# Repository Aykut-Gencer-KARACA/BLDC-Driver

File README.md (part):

<div align="center">

<br/>

<br/><br/>

**Sıfırdan tasarlanmış bir fırçasız DC (BLDC) motor sürücüsü.**<br/>
Hall sensörü olmadan, boştaki fazın back-EMF sıfır geçişini okuyarak rotor konumunu tahmin eder.

<br/>

<sub>PCB'nin Blender'da hazırlanmış 3D render'ı · tam çözünürlüklü video için görsele tıklayın</sub>

</div>

<!--
  ────────────────────────────────────────────────────────────────────────────
  OYNATILABİLİR VİDEO (isteğe bağlı)
  GitHub, repodaki .mp4 dosyalarını README içinde oynatıcı olarak GÖSTERMEZ.
  Oynatıcı istiyorsanız:
    1) GitHub'da README.md'yi web editöründe açın (kalem simgesi).
    2) assets/pcb-render.mp4 dosyasını editöre sürükleyip bırakın.
    3) Oluşan https://github.com/user-attachments/assets/... satırını
       aşağıdaki "VIDEO_LINKI_BURAYA" satırının yerine koyun (tek başına, kendi satırında).
    4) Bu yorum bloğunu silebilirsiniz.
  ────────────────────────────────────────────────────────────────────────────
-->

<!-- VIDEO_LINKI_BURAYA -->

## İçindekiler

- [Genel bakış](#-genel-bakış)
- [Öne çıkanlar](#-öne-çıkanlar)
- [Sistem mimarisi](#-sistem-mimarisi)
- [Six-step komütasyon](#-six-step-komütasyon)
- [Donanım](#-donanım)
- [Tasarım hesapları](#-tasarım-hesapları)
- [Pin haritası](#-pin-haritası)
- [PCB](#-pcb)
- [Firmware gereksinimleri](#-firmware-gereksinimleri)
- [Malzeme listesi](#-malzeme-listesi)
- [Depo yapısı](#-depo-yapısı)

## ◆ Genel bakış

Bu proje, bir **A2212 1000 KV** fırçasız motoru **3S LiPo** batarya ile sürmek için tasarlanmış bir ESC'dir (Electronic Speed Controller). Kart; güç girişi koruması, iki ayrı regülatör, 3 fazlı MOSFET köprüsü, faz başına bağımsız akım ölçümü, back-EMF algılama ve bir **STM32F405** mikrodenetleyiciyi tek bir PCB üzerinde topluyor.

Tasarımdaki her değer bir hesaba dayanıyor: MOSFET seçiminden bootstrap kondansatörüne, dead-time'dan ferrit bead bastırma oranına kadar kararların gerekçesi [Tasarım hesapları](#-tasarım-hesapları) bölümünde; tüm türetimler adım adım [Hesaplama Notları](Tactical%20Calculation%20Reports.pdf) dosyasında.

| Özellik | Değer |
|---|---|
| **Kontrol yöntemi** | Sensörsüz six-step (trapezoidal), back-EMF sıfır geçişi |
| **Giriş gerilimi** | 3S LiPo · 11.1 V nominal · 12.6 V maksimum |
| **Faz akımı** | 10 A sürekli · 12 A tepe (tasarım hedefi) |
| **Anahtarlama** | 30 kHz, center-aligned PWM |
| **Dead-time** | 2 katman: TIM1 DTG ≈ 1 µs + DRV8300 sabit ≈ 215 ns (tipik) |
| **Akım ölçümü** | 3 × low-side şönt (10 mΩ) + 3 × INA180A1 (20 V/V), eşzamanlı örnekleme |
| **Hız ayarı** | Panel montaj 10 kΩ potansiyometre |
| **Programlama** | SWD (ST-Link V2) |

## ◆ Öne çıkanlar

<table>
<tr>
<td width="50%" valign="top">

**Katmanlı giriş koruması**<br/>
TVS diyot (SMBJ20A, 32.4 V clamp), 20 A SMD sigorta ve P-kanal ters polarite MOSFET. Hot-plug ve anahtarlama kaynaklı gerilim darbelerine karşı koruma.

</td>
<td width="50%" valign="top">

**Faz başına eşzamanlı akım ölçümü**<br/>
Üç şönt akımı üç ayrı ADC'ye dağıtıldı (ADC1/2/3) ve her birinde **Rank 1** kanalı. TIM1 CH4 tetiklediği anda üç faz aynı anda örnekleniyor, fazlar arası zaman kayması yok.

</td>
</tr>
<tr>
<td valign="top">

**Isıl hesabı yapılmış MOSFET seçimi**<br/>
DON100N04 (40 V, < 3.5 mΩ, **Q<sub>g</sub> ≈ 40 nC** @ 10 V). 10.5 A'de MOSFET başına ≈ 0.39 W (25 °C); sıcakken (4.46 mΩ) ≈ 0.49 W ve 40 °C ortamda T<sub>J</sub> ≈ 65 °C. Bu kartta tek MOSFET'in ısıl sınırı ≈ 22 A.

</td>
<td valign="top">

**Temiz analog besleme**<br/>
VDDA hattı ferrit bead + 100 nF + 1 µF ile buck ripple'ından ayrıldı. 500 kHz'de tahmini **30–60 kat bastırma** (geçen kısım ≈ %1.6–3). ADC referansı ve CSA beslemesi aynı hattan: ölçüm oransal (ratiometric).

</td>
</tr>
<tr>
<td valign="top">

**Hesaplanmış bootstrap**<br/>
C<sub>BOOT,min</sub> ≈ 47 nF (TI'ın 1 V dalgalanma kuralı), seçilen 100 nF ile **~2× pay** ve ≈ 0.47 V dalgalanma. Üst kol kesintisiz açık kalamayacağı için %100 duty kullanılmıyor.

</td>
<td valign="top">

**Sanal nötr ile back-EMF algılama**<br/>
Faz başına 20 kΩ / 4.99 kΩ bölücü 12.6 V'u ≈ 2.52 V'a indiriyor; 3 × 20 kΩ + 1.65 kΩ'luk sanal nötr aynı ölçekte (sapma ≈ %0.7). Boştaki fazın nötrü kestiği an sıfır geçişi.

</td>
</tr>
</table>

## ◆ Sistem mimarisi

Güç yolu soldan sağa akıyor: batarya, sırasıyla sigorta (F1), TVS diyodu (D1) ve ters polarite MOSFET'inden (Q7) geçip `V_BUS` barasına ulaşıyor. Bu baradan üç kol ayrılıyor:

- **TPS54202 buck** → 3.3 V (MCU, CSA'lar, potansiyometre) · 500 kHz senkron
- **BA00BC0WFP LDO** → 8 V GVDD (DRV8300 gate sürme beslemesi) · ≈ 5 mA tipik, en fazla ≈ 11 mA yük
- **3 faz köprü** → motor fazları A / B / C

STM32, TIM1'in 6 tamamlayıcı PWM çıkışıyla DRV8300'ü sürüyor; DRV8300 de bootstrap üzerinden üst kol N-kanal MOSFET'lerin gate'lerini bara geriliminin üstüne taşıyor.

## ◆ Six-step komütasyon

Her elektriksel periyot altı adıma bölünüyor. Her adımda **iki faz aktif** (biri üst koldan PWM'leniyor, diğeri alt koldan sürekli iletimde), **üçüncü faz boşta** kalıyor. Boştaki fazın back-EMF'i sanal nötr seviyesini kestiği anda (sıfır geçişi) rotorun konumu biliniyor ve bir sonraki adıma geçiş zamanlanıyor.

| Adım | 1 | 2 | 3 | 4 | 5 | 6 |
|:--|:-:|:-:|:-:|:-:|:-:|:-:|
| **Üst kol (PWM)** | A | A | B | B | C | C |
| **Alt kol (açık)** | B | C | C | A | A | B |
| **Boşta (BEMF ölçümü)** | C | B | A | C | B | A |

> [!NOTE]
> Motor dururken back-EMF olmadığı için sensörsüz kontrolde **açık döngü başlatma** (open-loop ramp) gerekiyor. Motor yeterli hıza ulaşıp BEMF okunabilir hale geldiğinde kapalı döngüye geçiliyor.

## ◆ Donanım

<details open>
<summary><b>Güç katı</b></summary>
<br/>

| Blok | Parça | Not |
|---|---|---|
| Yarım köprü MOSFET'leri | 6 × **DON100N04** (DFN-8) | 40 V · < 3.5 mΩ · Q<sub>g</sub> ≈ 40 nC · gövde diyodu yeterli, harici Schottky yok |
| Gate dirençleri | 6 × 15 Ω | TI referans tasarımı ve bağımsız hesapla doğrulandı |
| Gate pull-down | 6 × 10 kΩ | Self turn-on koruması |
| Faz kondansatörleri | Faz başına 100 µF + 1 µF + 100 nF | Bulk + decoupling |

</details>

<details>
<summary><b>Gate sürücü — DRV8300</b></summary>
<br/>

- DT pini boşta (ya da GND'de): dahili dead-time ≈ 215 ns (tipik, datasheet)
- Bootstrap: 100 nF, entegre bootstrap diyodu
- GVDD: 8 V LDO çıkışı
- nFAULT çıkışı yok → donanımsal aşırı akım kesmesi (BKIN) yok; akım, şönt + INA180 zinciriyle ölçülüyor

</details>

<details>
<summary><b>Akım ölçümü</b></summary>
<br/>

- 3 × **10 mΩ / 3 W** şönt (2512), alt kol altında (low-side)
- 3 × **INA180A1** (20 V/V) — 12 A'de 2.4 V çıkış
- Çıkışta 100 Ω + 22 nF RC filtre (f<sub>c</sub> ≈ 72 kHz)
- 12-bit ADC ile çözünürlük ≈ **4 mA / LSB**

</details>

<details>
<summary><b>Back-EMF algılama</b></summary>
<br/>

- Faz başına bölücü: 20 kΩ / 4.99 kΩ → 12.6 V faz geriliminde **≈ 2.52 V** ADC girişi
- Sanal nötr: 3 × 20 kΩ yıldız + 1.65 kΩ (R<sub>n</sub> = R<sub>alt</sub>/3) → faz bölücüleriyle aynı ölçek
- Tüm dirençler ±%1; ölçek sapması ≈ %0.7

</details>

<details>
<summary><b>Mikrodenetleyici — STM32F405RGT6</b></summary>
<br/>

- Cortex-M4F · 168 MHz · 1 MB Flash · 192 KB RAM · FPU
- 8 MHz HSE kristal, 2 × 30 pF yük kondansatörü (C<sub>L</sub> = 20 pF)
- VCAP1/2: 2 × 2.2 µF X5R
- 4 × VDD'ye ayrı 100 nF, VBAT → 3.3 V + 100 nF
- NRST: 100 nF + tact switch · BOOT0: 10 kΩ ile GND
- SWD: 4 pinlik 2.54 mm header (3.3 V, SWDIO, SWCLK, GND)

</details>

<details>
<summary><b>Göstergeler (LED)</b></summary>
<br/>

| LED | Görev | Sürüş | Akım |
|---|---|---|---|
| LED1 | Güç göstergesi | 3.3 V → R38 (200 Ω) → LED1 → GND | ≈ 6.5 mA |
| LED2 | SWD aktivite göstergesi | 3.3 V → R39 (200 Ω) → LED2 → Q8 (MMBT5551, low-side) · baz SWCLK'ten R40 (10 kΩ) ile | ≈ 6.5 mA |

- LED2, debugger bağlıyken SWCLK üzerindeki trafikle yanıp söner; MCU pini harcamaz.
- Q8'in baz akımı ≈ 0.26 mA — SWCLK hattını anlamlı ölçüde yüklemez.

</details>

## ◆ Tasarım hesapları

<details>
<summary><b>Giriş koruması: sigorta, ters polarite MOSFET'i, TVS</b></summary>
<br/>

**Sigorta (F1).** 20 A, gecikmeli (time-lag), 32 V DC. Gecikmeli olması motorun kalkış anındaki kısa süreli yüksek akımda gereksiz atmayı önler; 20 A, 10 A'lik çalışma akımının iki katıdır.

**Ters polarite MOSFET'i (Q7).** Kayıp karşılaştırması, R<sub>DS(on)</sub> = 3.1 mΩ ile:

$$\text{Q7 ile: } P = I^2 \times R_{DS(on)} = 10^2 \times 0.0031 \approx 0.31\text{ W}$$

$$\text{Schottky diyotla: } P = V_F \times I \approx 0.45\text{ V} \times 10\text{ A} \approx 4.5\text{ W}$$

Fark yaklaşık 15 kattır. Q7'nin gate–source arasına en fazla 12.6 V gelir; HSBA4119'un V<sub>GS</sub> sınırı ±20 V, V<sub>DS</sub> sınırı −40 V'tur.

**TVS (D1, SMBJ20A).** 20 V'a kadar neredeyse hiç akım çekmez; darbeyi en fazla 32.4 V'ta kenetler (V<sub>BR</sub> = 22.2–24.5 V, I<sub>PP</sub> = 18.6 A'de V<sub>C</sub> = 32.4 V). Bu değer 40 V'luk MOSFET'lerin altında kaldığı için onları korur; ama bataryadan doğrudan beslenen BA00BC0WFP (girişi en fazla 18 V) ve TPS54202 (en fazla 30 V) bu seviyede tam korunmaz. 3S'te normal gerilim 12.6 V olduğundan bu yalnızca ciddi bir darbede söz konusudur.

**Ters bağlantıda D1.** D1 tek yönlü bir TVS'tir ve şemada Q7'nin önünde, batarya tarafındadır. Ters bağlantıda Q7 köprüyü korur, ama D1 ileri yönde iletir ve bataryayı F1 üzerinden kısa devre eder; F1 atar. Kart zarar görmez, yalnızca sigorta değiştirilir.

</details>

<details>
<summary><b>MOSFET seçimi</b></summary>
<br/>

Anahtarlama anında akım bir MOSFET'ten diğerine devredilirken yoldaki parazit endüktans aşım üretir:

$$\Delta V \approx L_{\text{parazit}} \times \frac{di}{dt} \qquad\text{(örnek: } 10\text{ nH} \times 0.5\text{ A/ns} = 5\text{ V)}$$

Bu yüzden pratikte bara geriliminin en az 2 katı alınır:

$$V_{DS} \geq 2 \times V_{\text{bara,max}} = 2 \times 12.6\text{ V} = 25.2\text{ V} \quad\Rightarrow\quad 40\text{ V sınıfı}$$

$$I_D \geq 3 \times I_{\text{çalışma}} = 3 \times 10\text{ A} = 30\text{ A} \quad\Rightarrow\quad \text{DON100N04: 100 A}$$

İletim kaybı, 25 °C'de $R_{DS(on)} \leq 3.5\text{ m}\Omega$ ile:

$$P = I^2 \times R_{DS(on)} = 10.5^2 \times 0.0035 \approx 0.39\text{ W}$$

Asıl karar ısıl hesapla verilir. Datasheet'teki 100 A (T<sub>C</sub> = 25 °C) ve 59 A (T<sub>C</sub> = 125 °C) değerleri, sonsuz soğutucu varsayımıyla (R<sub>θCA</sub> = 0) yapılmış ısı hesabıdır: $P_{max} = 25/1.6 \approx 15.6\text{ W}$, $I_D = \sqrt{15.6/0.00446} \approx 59\text{ A}$. Bu kartta soğutucu yoktur; ısı PCB bakırından havaya atılır. Sıcakken (150 °C) direnç ≈ 4.46 mΩ, R<sub>θJA</sub> = 50 °C/W ve T<sub>A</sub> = 40 °C ile:

$$P = 10.5^2 \times 0.00446 \approx 0.49\text{ W} \quad\Rightarrow\quad T_J = T_A + P \times R_{\theta JA} = 40 + 0.49 \times 50 \approx 65\text{ °C}$$

$$I_{max} = \sqrt{\frac{(150 - 40)/50}{0.00446}} = \sqrt{\frac{2.2\text{ W}}{0.00446\ \Omega}} \approx 22\text{ A}$$

Yani bu kartta tek bir MOSFET'in sürekli taşıyabileceği akım datasheet'teki 100 A değil, yaklaşık 22 A'dir. Datasheet'teki en kötü parça (25 °C'de 3.5 mΩ, tipikten ≈ 1.25 kat dirençli) için P ≈ 0.61 W ve T<sub>J</sub> ≈ 71 °C olur; sonuç değişmez. Six-step'te bir MOSFET bir elektriksel turun yalnızca bir kısmında akım taşıdığı için gerçek ortalama ısı bundan da düşüktür.

</details>

<details>
<summary><b>Bara kondansatörleri</b></summary>
<br/>

Üst MOSFET her açıldığında motor akımı (≈ 10 A) bir anda bu kola akmak ister; batarya kablo ve PCB izlerinin endüktansı yüzünden bu ani talebe yetişemez. Bu yüzden her kolun yanına faz başına 100 µF + 1 µF + 100 nF konur: 100 µF'lık elektrolitik yükün büyük kısmını depolar, 1 µF ve 100 nF'lık seramikler MHz mertebesindeki hızlı akım değişimlerini karşılar. Kondansatörlerin MOSFET'lerin dibinde olması hızlı akım döngüsünü kısaltır, aşımı azaltır. Motor sargısı bu döngünün içinde değildir; endüktansı büyük olduğu için anahtarlama süresince sabit bir akım kaynağı gibi davranır.

</details>

<details>
<summary><b>Gate sürme: neden sürücü, gate direnci, tepe ve ortalama akım</b></summary>
<br/>

STM32 MOSFET'leri doğrudan süremez:

1. **Gerilim yetmez:** pin en fazla 3.3 V verir; MOSFET'in R<sub>DS(on)</sub> değeri 4.5 V ve 10 V için verilmiştir.
2. **Akım yetmez:** 40 nC'luk gate'i bir GPIO'nun 25 mA'iyle doldurmak $t \approx Q_g / I = 40\text{ nC} / 25\text{ mA} \approx 1.6\ \mu\text{s}$ sürer; DRV8300'ün 0.75 A'iyle aynı süre ≈ 53 ns'dir.
3. **Üst MOSFET'in gate'i baranın üstüne çıkmalı:** source 12.6 V'a çıkınca gate ≈ 20 V civarında olmalıdır; bunu sürücü bootstrap devresiyle üretir.

15 Ω seri gate direnci gate'in dolma hızını yumuşatır (di/dt ve aşım düşer) ve sürücünün tepe akımını sınırlar; daha büyük direnç daha yumuşak ama daha yavaş (daha sıcak) anahtarlama demektir. 10 kΩ pull-down gate'i source seviyesinde tutar.

$$I_{\text{tepe}} = \frac{V_{GVDD}}{R_{toplam}} = \frac{8\text{ V}}{15\ \Omega} \approx 0.53\text{ A}$$

Sürücünün ve MOSFET'in iç dirençleri eklendiği için gerçek tepe akım bunun biraz altında kalır; DRV8300'ün 750 mA'lik (tipik) açma ve 1.5 A'lik kapama akımının altındadır.

$$I_{\text{ort}} \approx \frac{I_{\text{tepe}}}{2} = \frac{0.53}{2} \approx 0.27\text{ A} \qquad t_{\text{şarj}} \approx \frac{Q_g}{I_{\text{ort}}} = \frac{32\text{ nC}}{0.27\text{ A}} \approx 120\text{ ns}$$

120 ns, 30 kHz'lik PWM periyodunun (33 µs) binde dördü kadardır. Gate 8 V ile sürüldüğü için taşınan yük ≈ 32 nC'dur; hesaplarda 40 nC kullanmak güvenli taraftır.

</details>

<details>
<summary><b>Bootstrap kondansatörü</b></summary>
<br/>

Üst kol MOSFET'ini iletimde tutmak için gate'in source'un 8 V üstünde olması gerekir; source bara gerilimine (12.6 V) fırladığı için gate sabit 8 V ile sürülemez. Gate, SH ile birlikte yükselip alçalan bir kondansatörden (C<sub>boot</sub>) beslenir:

- **Şarj fazı:** alt MOSFET iletimdeyken SH ≈ 0 V; GVDD, DRV8300 içindeki bootstrap diyodu üzerinden kondansatörü doldurur. Diyot düşümü (en fazla 0.85 V) yüzünden kondansatörde 8 − 0.85 ≈ 7.15 V birikir.
- **Sürüş fazı:** üst MOSFET iletime geçer, SH 12.6 V'a çıkar; kondansatörün üst ucu 12.6 + 7.15 ≈ 19.8 V'ta kalır ve gate bu noktadan beslenir.

Kondansatörün boyutu (TI'ın yöntemiyle, V<sub>GVDD</sub> = 8 V, Q<sub>g</sub> = 40 nC, f<sub>sw</sub> = 30 kHz):

$$\Delta V_{BST} = V_{GVDD} - V_{BOOTD} - V_{BSTUV} = 8 - 0.85 - 4.5 = 2.65\text{ V}$$

$$Q_{tot} = Q_g + \frac{I_{LBS,TRAN}}{f_{sw}} = 40\text{ nC} + \frac{220\ \mu\text{A}}{30\text{ kHz}} \approx 47\text{ nC}$$

TI, kondansatör üzerindeki çevrim başına dalgalanmanın 1 V'u geçmemesini öneriyor:

$$C_{BOOT,min} = \frac{Q_{tot}}{1\text{ V}} \approx 47\text{ nF} \quad\Rightarrow\quad 100\text{ nF seçildi (yaklaşık 2 kat pay)}$$

100 nF ile dalgalanma $47\text{ nC} / 100\text{ nF} \approx 0.47\text{ V}$, yani 2.65 V'luk sınırın çok altında. GVDD tarafında kural $C_{GVDD} \geq 10 \times C_{BOOT} = 1\ \mu\text{F}$; datasheet GVDD pininde ayrıca en az 10 µF istiyor (C43 = 10 µF, C40 = 1 µF, C42 = 100 nF).

</details>

<details>
<summary><b>GVDD akım bütçesi ve LDO</b></summary>
<br/>

8 V'un gerekçesi: MOSFET tam açılmalı (8 V, datasheet'in R<sub>DS(on)</sub> verdiği 10 V'a yakındır), sürücünün GVDD kilidinden (4.35 V) uzak durulmalı ve batarya boşalırken gate sürüşü sabit kalmalı. Akım çok küçük (≈ 11 mA) olduğu için LDO'nun kaybı önemsizdir.

Six-step'te her an yalnızca PWM uygulanan koldaki iki MOSFET anahtarlanır:

$$I_{\text{gate}} = 2 \times Q_g \times f_{sw} = 2 \times 40\text{ nC} \times 30\text{ kHz} = 2.4\text{ mA}$$

(Altı MOSFET'in birden anahtarlandığı en kötü durumda 7.2 mA.) Üst kol gate yükü bootstrap kondansatöründen akar; ama her çevrimde gate'e giden 40 nC bir sonraki şarj fazında GVDD'den yeniden alındığı için bütçeye dahildir.

| Kalem | Tipik | En fazla |
|---|---|---|
| DRV8300 kendi tüketimi | 0.83 mA | 1.4 mA |
| Gate'leri doldurmak | 2.4 mA | 7.2 mA |
| Bootstrap tüketimi (3 kanal) | 0.32 mA | 0.66 mA |
| Gate pull-down'lar (2 MOSFET iletimde, 8 V / 10 kΩ) | 1.6 mA | 1.6 mA |
| **Toplam** | **≈ 5.2 mA** | **≈ 10.9 mA** |

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
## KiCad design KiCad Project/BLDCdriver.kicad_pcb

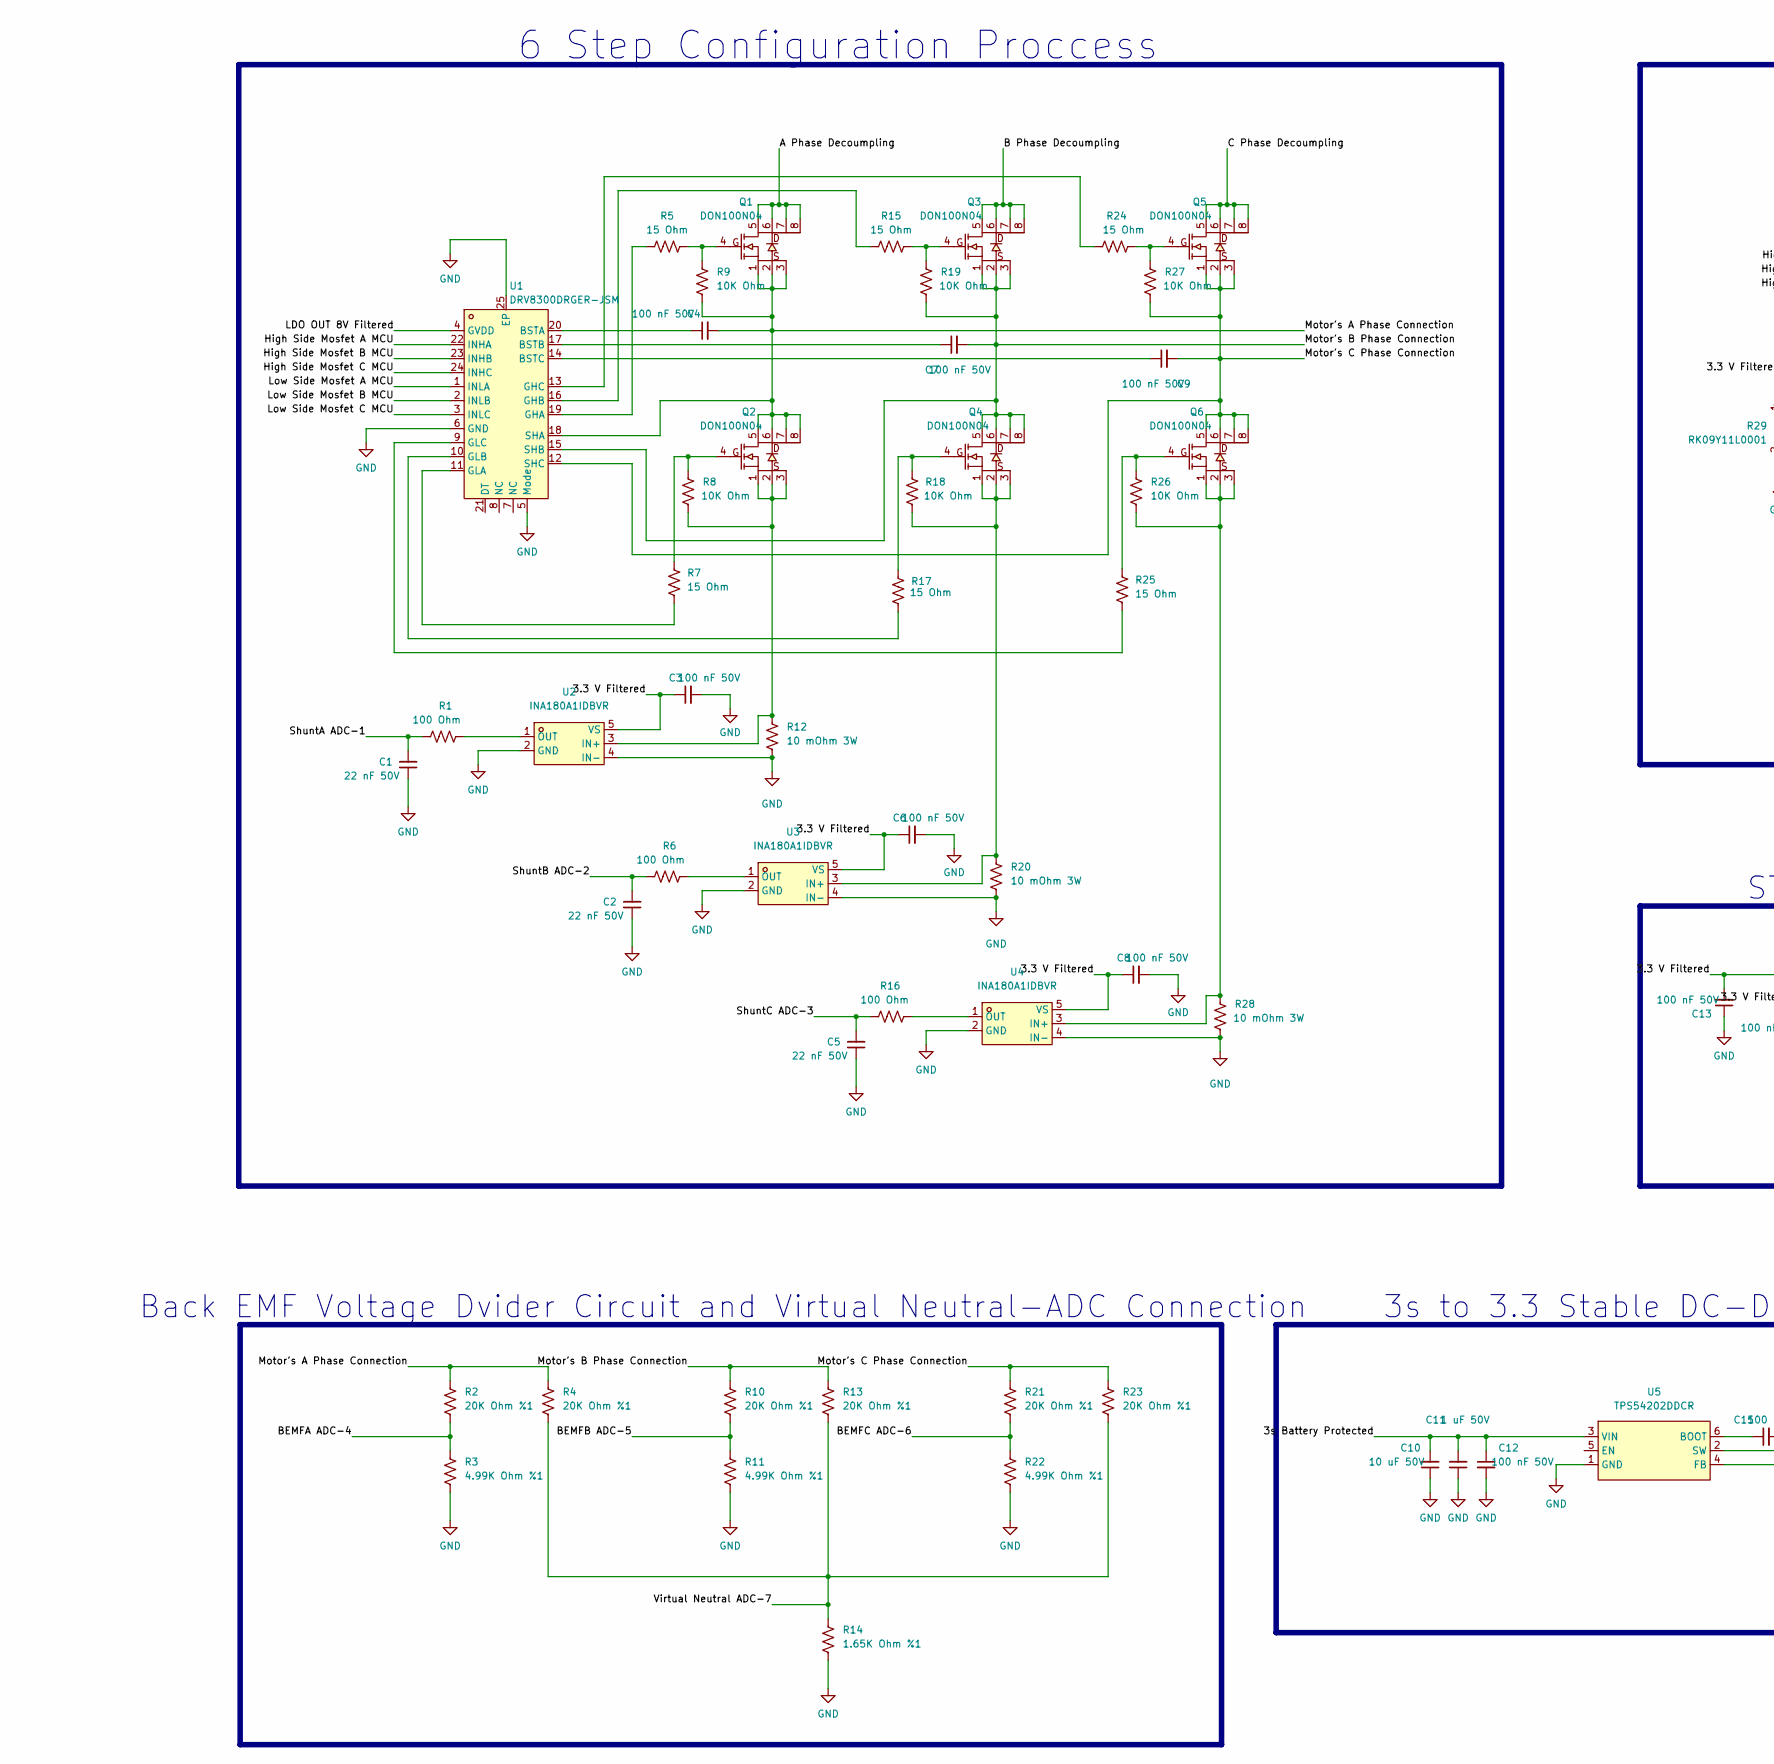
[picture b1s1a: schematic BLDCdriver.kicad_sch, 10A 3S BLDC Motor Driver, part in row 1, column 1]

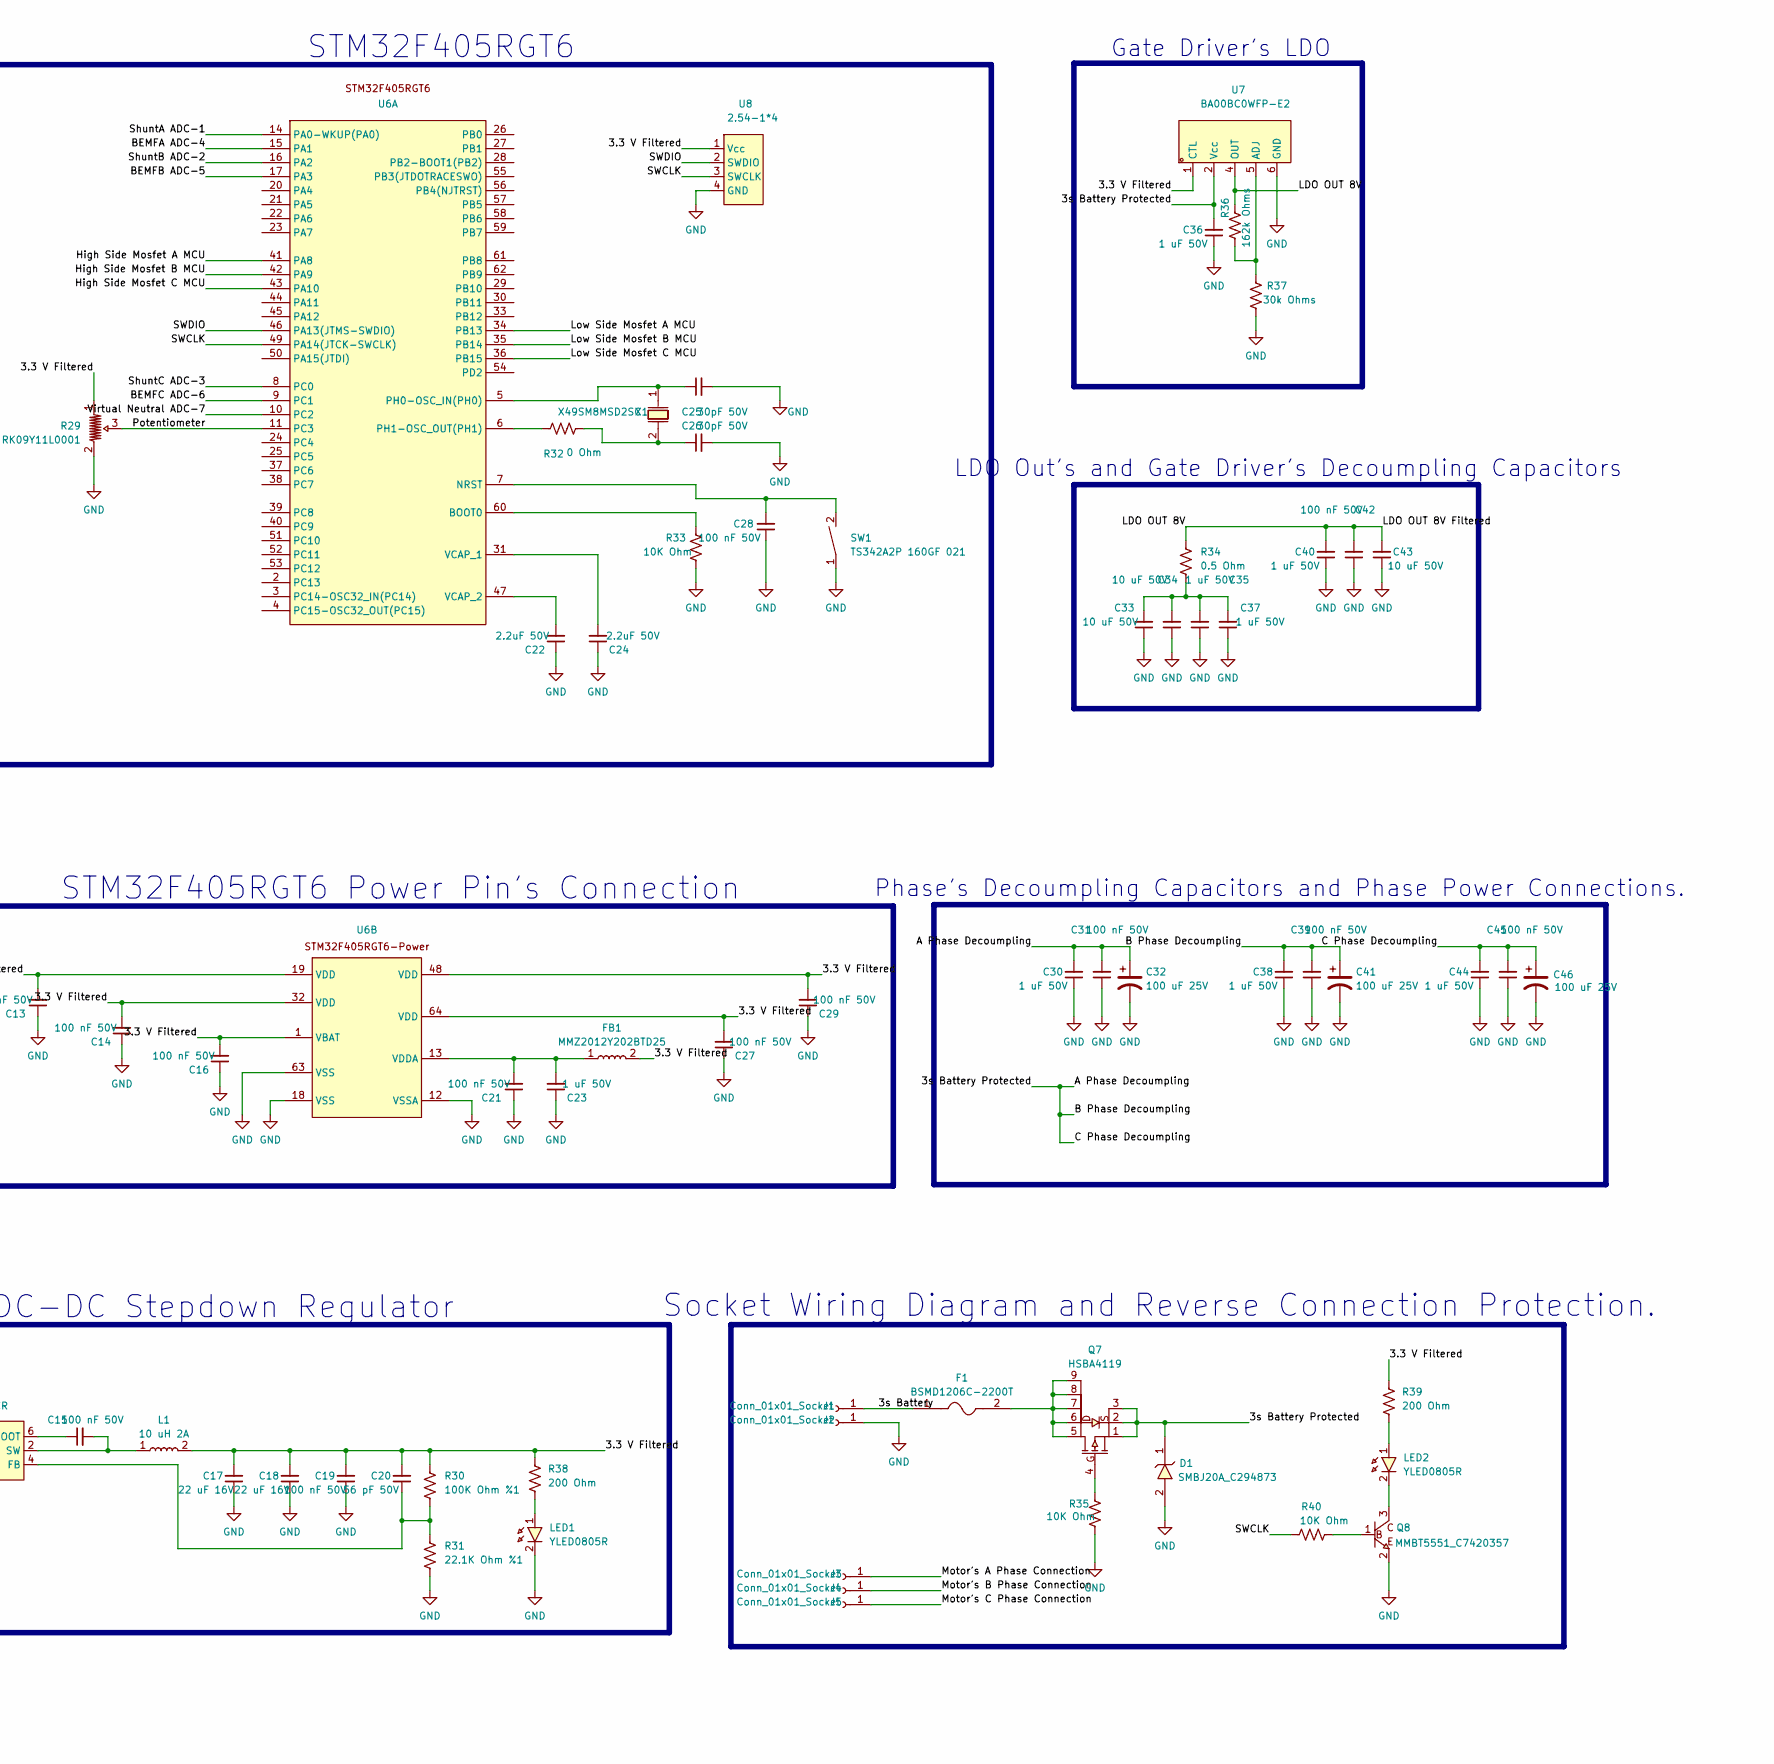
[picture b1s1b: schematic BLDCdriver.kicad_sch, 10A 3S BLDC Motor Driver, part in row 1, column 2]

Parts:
C1, C2, C5: 22 nF 50V; C_0603_1608Metric; LCSC Part C21122
C3, C4, C6, C7, C8, C9, C12, C13, C14, C15, C16, C19, C21, C27, C28, C29, C31, C39, C42, C45: 100 nF 50V; C_0603_1608Metric; LCSC Part C14663
C10, C33, C34, C43: 10 uF 50V; C_1206_3216Metric; LCSC Part C13585
C11, C23, C30, C35, C36, C37, C38, C40, C44: 1 uF 50V; C_0603_1608Metric; LCSC Part C5199872
C17, C18: 22 uF 16V; C_1206_3216Metric; LCSC Part C5448976
C20: 56 pF 50V; C_0603_1608Metric; LCSC Part C107053
C22, C24: 2.2uF 50V; C_0603_1608Metric; LCSC Part C913904
C25, C26: 30pF 50V; C_0603_1608Metric; LCSC Part C113797
C32, C41, C46: 100 uF 25V; CP_Elec_6.3x7.7; LCSC Part C46528102
D1: SMBJ20A_C294873; SMB_L4.6-W3.6-LS5.3-RD; LCSC Part C294873
F1: BSMD1206C-2200T; F1206; LCSC Part C41398512
FB1: MMZ2012Y202BTD25; L0805; LCSC Part C360718
J1, J2, J3, J4, J5: Conn_01x01_Socket; SolderWirePad_1x01_SMD_3x6mm
L1: 10 uH 2A; IND-SMD_L5.4-W5.1; LCSC Part C325986
LED1, LED2: YLED0805R; LED0805-R-RD_RED; LCSC Part C19171391
Q1, Q2, Q3, Q4, Q5, Q6: DON100N04; DFN-8_L5.8-W4.9-P1.27-LS6.1-BL-2; LCSC Part C41430596
Q7: HSBA4119; DFN-8_L5.7-W5.1-P1.27-LS6.1-BL; LCSC Part C22359242
Q8: MMBT5551_C7420357; SOT-23-3_L2.9-W1.3-P1.90-LS2.4-BR; LCSC Part C7420357
R1, R6, R16: 100 Ohm; R_0805_2012Metric; LCSC Part C17408
R2, R4, R10, R13, R21, R23: 20K Ohm %1; R_0805_2012Metric; LCSC Part C2907240
R3, R11, R22: 4.99K Ohm %1; R_0805_2012Metric; LCSC Part C2933454
R5, R7, R15, R17, R24, R25: 15 Ohm; R_0805_2012Metric; LCSC Part C17480
R8, R9, R18, R19, R26, R27, R33, R35, R40: 10K Ohm; R_0805_2012Metric; LCSC Part C2907219
R12, R20, R28: 10 mOhm 3W; R_2512_6332Metric; LCSC Part C5375464
R14: 1.65K Ohm %1; R_0805_2012Metric; LCSC Part C2933334
R29: RK09Y11L0001; RES-ADJ-TH_RK09Y11L0001; LCSC Part C470717
R30: 100K Ohm %1; R_0805_2012Metric; LCSC Part C149504
R31: 22.1K Ohm %1; R_0805_2012Metric; LCSC Part C17552
R32: 0 Ohm; R_0805_2012Metric; LCSC Part C17477
R34: 0.5 Ohm; R_0805_2012Metric; LCSC Part C2934267
R36: 162k Ohms; R_0805_2012Metric; LCSC Part C17486
R37: 30k Ohms; R_0805_2012Metric; LCSC Part C2907255
R38, R39: 200 Ohm; R_0805_2012Metric; LCSC Part C2907239
SW1: TS342A2P 160GF 021; KEY-SMD_L3.9-W3.0-LS5.0; LCSC Part C5373431
U1: DRV8300DRGER-JSM; QFN-24_L4.0-W4.0-P0.50-BL-EP2.7; LCSC Part C3655801
U2, U3, U4: INA180A1IDBVR; SOT-23-5_L3.0-W1.7-P0.95-LS2.8-BR; LCSC Part C122228
U5: TPS54202DDCR; SOT-23-6_L2.9-W1.6-P0.95-LS2.8-BL; LCSC Part C191884
U6: LQFP-64_L10.0-W10.0-P0.50-LS12.0-BL; LCSC Part C15742
U7: BA00BC0WFP-E2; TO-252-5_L6.5-W5.5-P1.30-LS10.0-BR; LCSC Part C308578
U8: 2.54-1*4; HDR-TH_4P-P2.54-V-M-1; LCSC Part C5116483
X1: X49SM8MSD2SC; CRYSTAL-SMD_L11.5-W4.8-LS12.7; LCSC Part C12674

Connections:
/3.3 V Filtered: C3.1, C6.1, C8.1, C13.2, C14.2, C16.2, C17.2, C18.2, C19.2, C20.2, C27.2, C29.2, FB1.2, L1.2, R29.1, R30.1, R38.1, R39.1, U2.5 (VS), U3.5 (VS), U4.5 (VS), U6.1 (VBAT), U6.19 (VDD), U6.32 (VDD), U6.48 (VDD), U6.64 (VDD), U7.1 (CTL), U8.1 (Vcc)
/3s Battery: F1.1, J1.1 (Pin_1_1)
/3s Battery Protected: C10.2, C11.2, C12.1, C30.2, C31.2, C32.1, C36.2, C38.2, C39.2, C41.1, C44.2, C45.2, C46.1, D1.1, Q1.5, Q1.6, Q1.7, Q1.8, Q3.5, Q3.6, Q3.7, Q3.8, Q5.5, Q5.6, Q5.7, Q5.8, Q7.1, Q7.2, Q7.3, U5.3 (VIN), U7.2 (Vcc)
/BEMFA ADC-4: R2.2, R3.1, U6.15 (PA1)
/BEMFB ADC-5: R10.2, R11.1, U6.17 (PA3)
/BEMFC ADC-6: R21.2, R22.1, U6.9 (PC1)
/High Side Mosfet A MCU: U1.22 (INHA), U6.41 (PA8)
/High Side Mosfet B MCU: U1.23 (INHB), U6.42 (PA9)
/High Side Mosfet C MCU: U1.24 (INHC), U6.43 (PA10)
/LDO OUT 8V: C40.2, C42.2, C43.2, R34.1, R36.1, U1.4 (GVDD), U7.4 (OUT)
/Low Side Mosfet A MCU: U1.1 (INLA), U6.34 (PB13)
/Low Side Mosfet B MCU: U1.2 (INLB), U6.35 (PB14)
/Low Side Mosfet C MCU: U1.3 (INLC), U6.36 (PB15)
/Motor's A Phase Connection: C4.2, J3.1 (Pin_1_1), Q1.1, Q1.2, Q1.3, Q2.5, Q2.6, Q2.7, Q2.8, R2.1, R4.1, R9.2, U1.18 (SHA)
/Motor's B Phase Connection: C7.2, J4.1 (Pin_1_1), Q3.1, Q3.2, Q3.3, Q4.5, Q4.6, Q4.7, Q4.8, R10.1, R13.1, R19.2, U1.15 (SHB)
/Motor's C Phase Connection: C9.2, J5.1 (Pin_1_1), Q5.1, Q5.2, Q5.3, Q6.5, Q6.6, Q6.7, Q6.8, R21.1, R23.1, R27.2, U1.12 (SHC)
/Potentiometer: R29.3, U6.11 (PC3)
/SWCLK: R40.1, U6.49 (PA14(JTCK-SWCLK)), U8.3 (SWCLK)
/SWDIO: U6.46 (PA13(JTMS-SWDIO)), U8.2 (SWDIO)
/ShuntA ADC-1: C1.2, R1.1, U6.14 (PA0-WKUP(PA0))
/ShuntB ADC-2: C2.2, R6.1, U6.16 (PA2)
/ShuntC ADC-3: C5.2, R16.1, U6.8 (PC0)
/Virtual Neutral ADC-7: R4.2, R13.2, R14.1, R23.2, U6.10 (PC2)
GND: C1.1, C2.1, C3.2, C5.1, C6.2, C8.2, C10.1, C11.1, C12.2, C13.1, C14.1, C16.1, C17.1, C18.1, C19.1, C21.1, C22.1, C23.1, C24.1, C25.2, C26.2, C27.1, C28.1, C29.1, C30.1, C31.1, C32.2, C33.1, C34.1, C35.1, C36.1, C37.1, C38.1, C39.1, C40.1, C41.2, C42.1, C43.1, C44.1, C45.1, C46.2, D1.2, J2.1 (Pin_1_1), LED1.2, Q8.2, R3.2, R11.2, R12.2, R14.2, R20.2, R22.2, R28.2, R29.2, R31.2, R33.2, R35.2, R37.1, SW1.1, U1.5 (Mode), U1.6 (GND), U1.25 (EP), U2.2 (GND), U2.4 (IN-), U3.2 (GND), U3.4 (IN-), U4.2 (GND), U4.4 (IN-), U5.1 (GND), U6.12 (VSSA), U6.18 (VSS), U6.63 (VSS), U7.6 (GND), U8.4 (GND)
unnamed: C26.1, R32.2, X1.2
unnamed: C33.2, C34.2, C35.2, C37.2, R34.2
unnamed: F1.2, Q7.5, Q7.6, Q7.7, Q7.8, Q7.9
unnamed: LED1.1, R38.2
unnamed: LED2.1, R39.2
unnamed: LED2.2, Q8.3
unnamed: Q1.4, R5.2, R9.1
unnamed: Q2.4, R7.1, R8.1
unnamed: Q3.4, R15.2, R19.1
unnamed: Q4.4, R17.1, R18.1
unnamed: Q5.4, R24.2, R27.1
unnamed: Q6.4, R25.1, R26.1
unnamed: Q7.4, R35.1
unnamed: Q8.1, R40.2
unnamed: C4.1, U1.20 (BSTA)
unnamed: C7.1, U1.17 (BSTB)
unnamed: C9.1, U1.14 (BSTC)
unnamed: R5.1, U1.19 (GHA)
unnamed: R15.1, U1.16 (GHB)
unnamed: R24.1, U1.13 (GHC)
unnamed: R7.2, U1.11 (GLA)
unnamed: R17.2, U1.10 (GLB)
unnamed: R25.2, U1.9 (GLC)
unnamed: Q2.1, Q2.2, Q2.3, R8.2, R12.1, U2.3 (IN+)
unnamed: R1.2, U2.1 (OUT)
unnamed: Q4.1, Q4.2, Q4.3, R18.2, R20.1, U3.3 (IN+)
unnamed: R6.2, U3.1 (OUT)
unnamed: Q6.1, Q6.2, Q6.3, R26.2, R28.1, U4.3 (IN+)
unnamed: R16.2, U4.1 (OUT)
unnamed: C15.1, U5.6 (BOOT)
unnamed: C20.1, R30.2, R31.1, U5.4 (FB)
unnamed: C15.2, L1.1, U5.2 (SW)
unnamed: R33.1, U6.60 (BOOT0)
unnamed: C28.2, SW1.2, U6.7 (NRST)
unnamed: C25.1, U6.5 (PH0-OSC_IN(PH0)), X1.1
unnamed: R32.1, U6.6 (PH1-OSC_OUT(PH1))
unnamed: C24.2, U6.31 (VCAP_1)
unnamed: C22.2, U6.47 (VCAP_2)
unnamed: C21.2, C23.2, FB1.1, U6.13 (VDDA)
unnamed: R36.2, R37.2, U7.5 (ADJ)

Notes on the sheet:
Gate Driver's LDO
6 Step Configuration Proccess
Back EMF Voltage Dvider Circuit and Virtual Neutral-ADC Connection
LDO Out's and Gate Driver's Decoumpling Capacitors
STM32F405RGT6 Power Pin's Connection
Phase's Decoumpling Capacitors and Phase Power Connections.
Socket Wiring Diagram and Reverse Connection Protection.
3s to 3.3 Stable DC-DC Stepdown Regulator
STM32F405RGT6

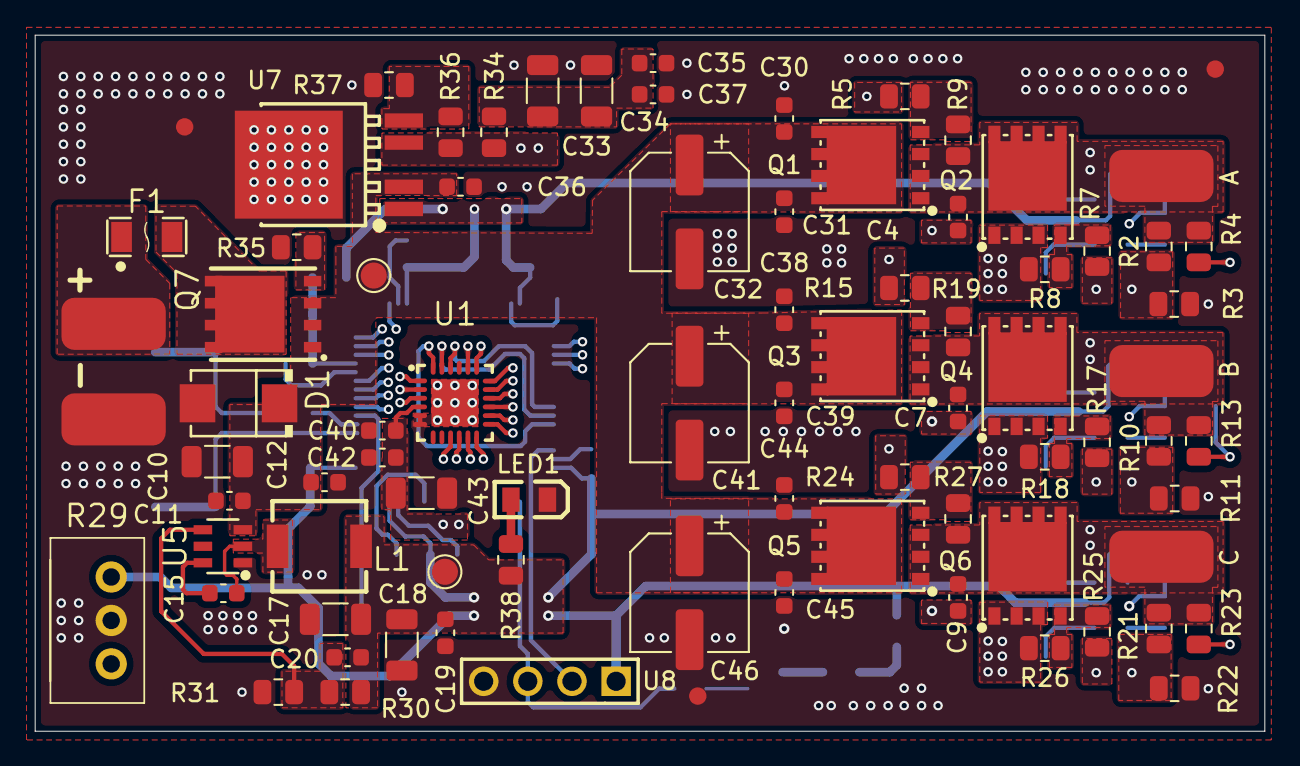
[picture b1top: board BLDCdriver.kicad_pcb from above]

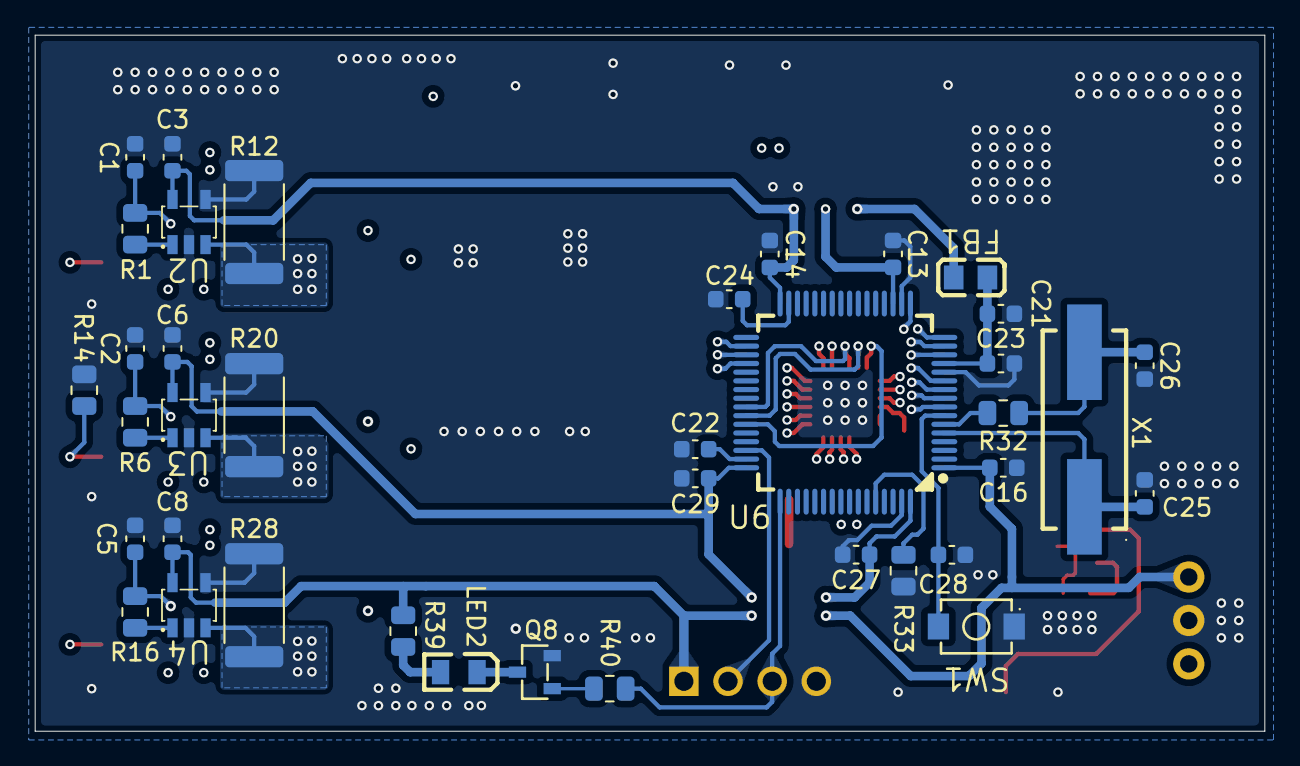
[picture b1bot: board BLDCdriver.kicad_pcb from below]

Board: 6 copper layers, 70.8 x 40.0 mm, 115 parts (38 on the bottom side), 64 nets.
